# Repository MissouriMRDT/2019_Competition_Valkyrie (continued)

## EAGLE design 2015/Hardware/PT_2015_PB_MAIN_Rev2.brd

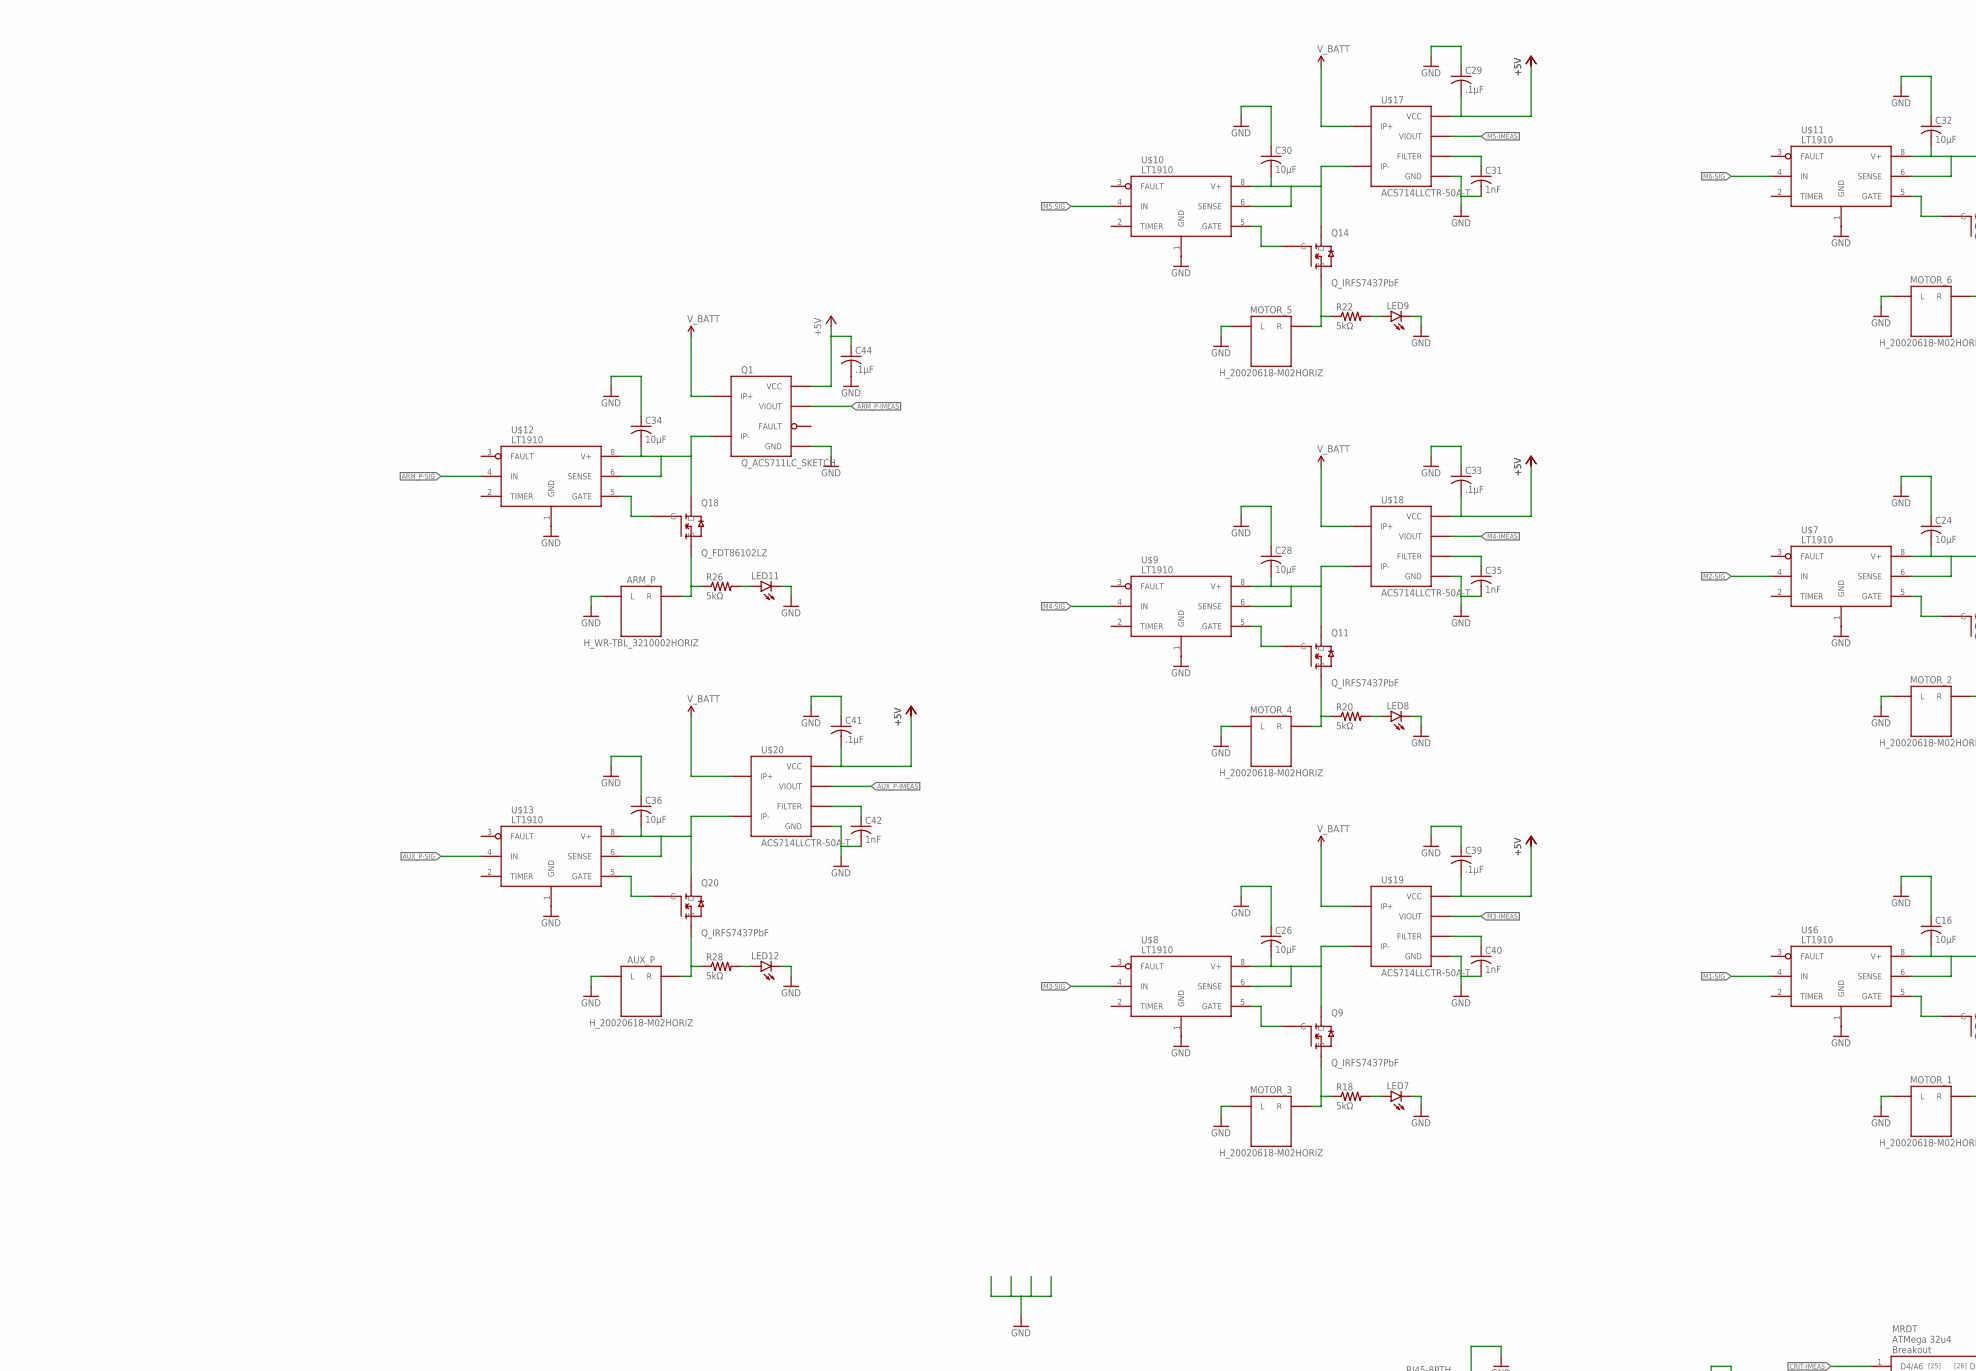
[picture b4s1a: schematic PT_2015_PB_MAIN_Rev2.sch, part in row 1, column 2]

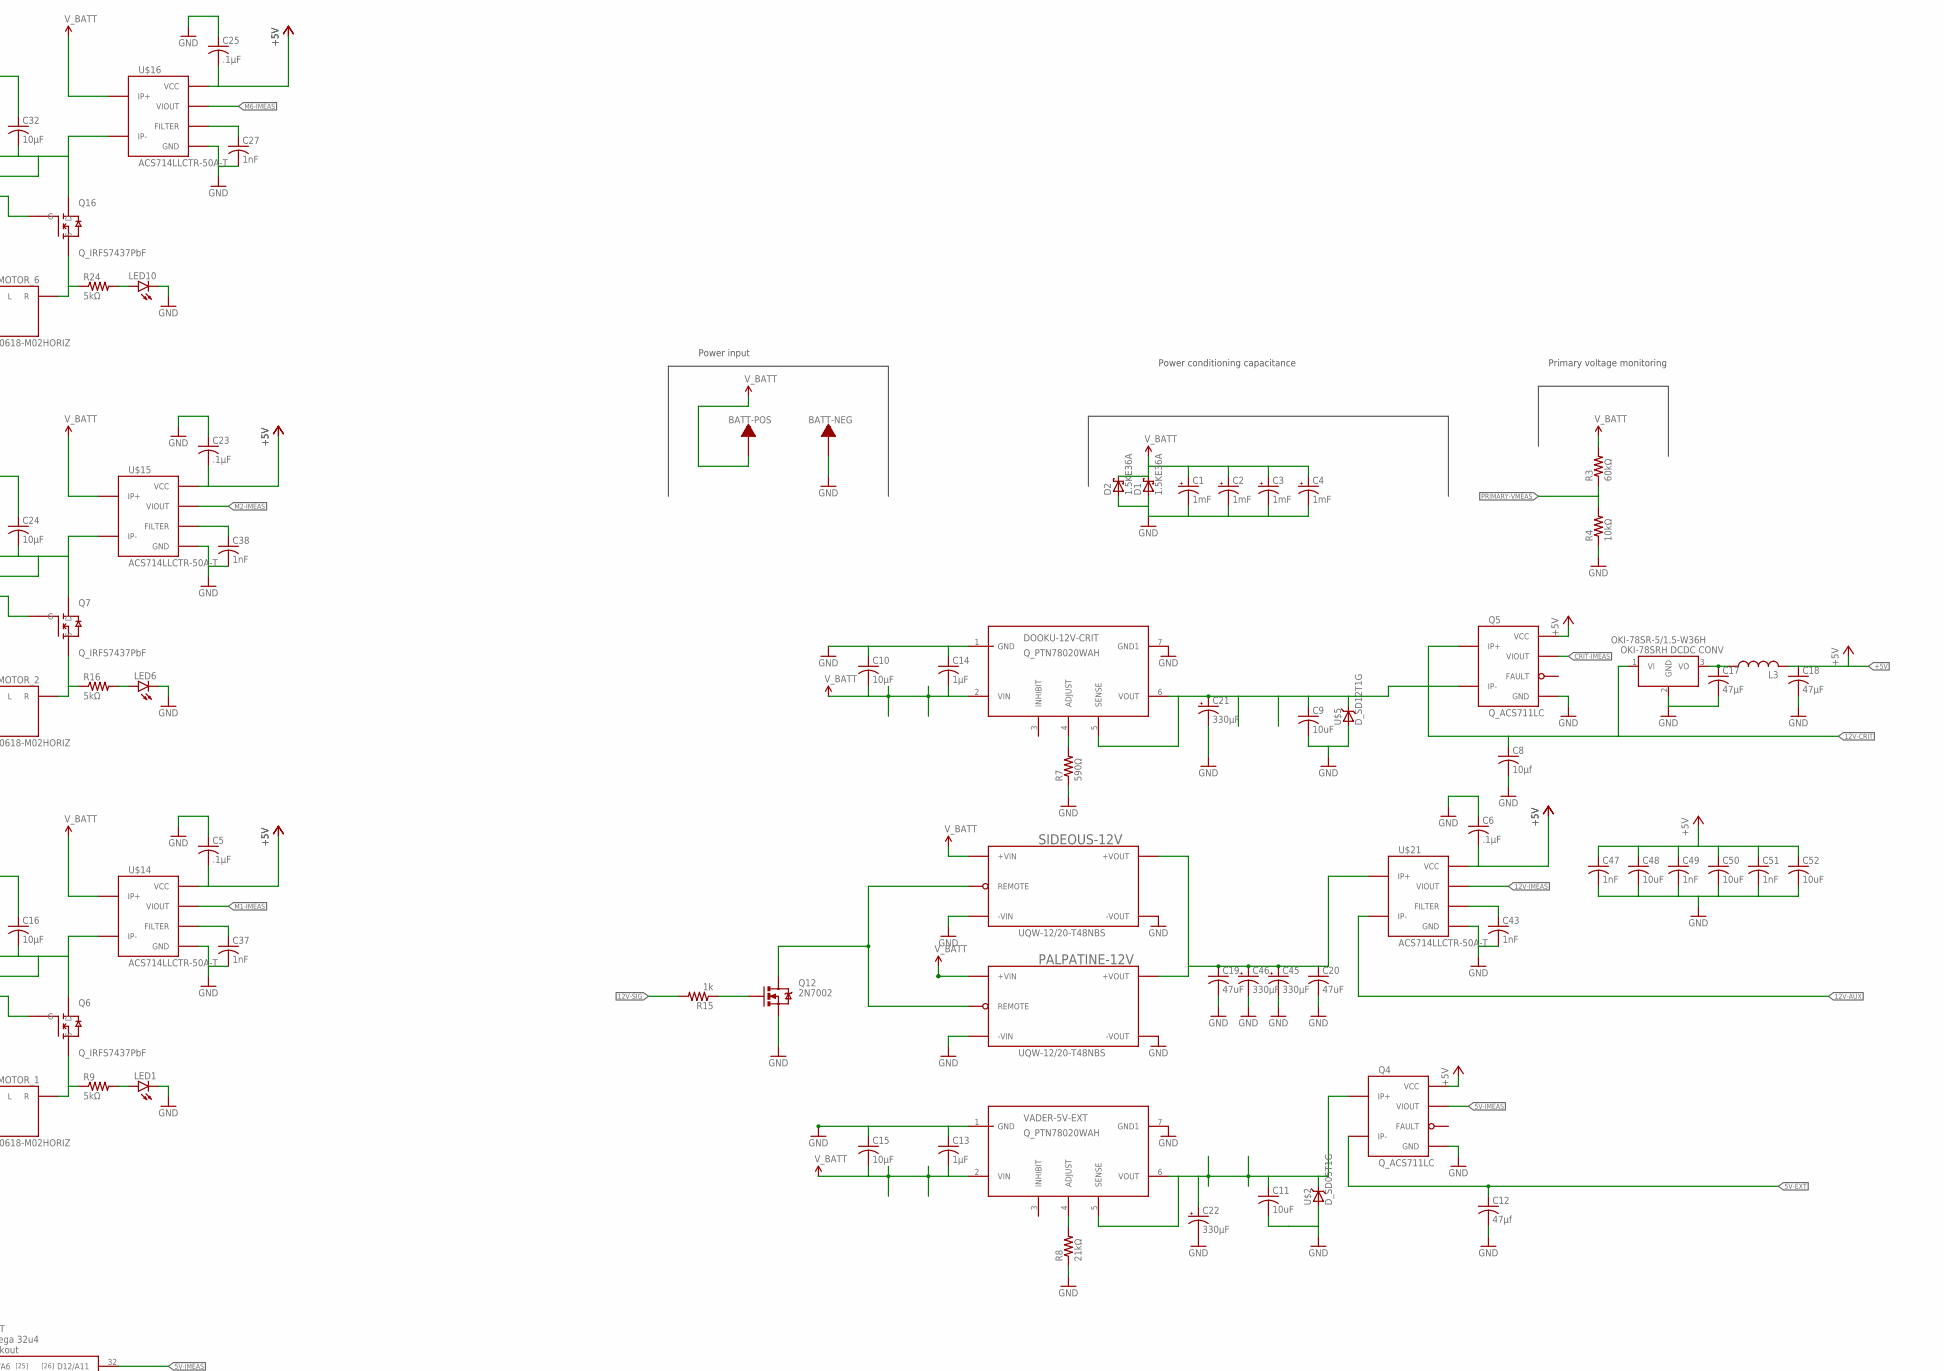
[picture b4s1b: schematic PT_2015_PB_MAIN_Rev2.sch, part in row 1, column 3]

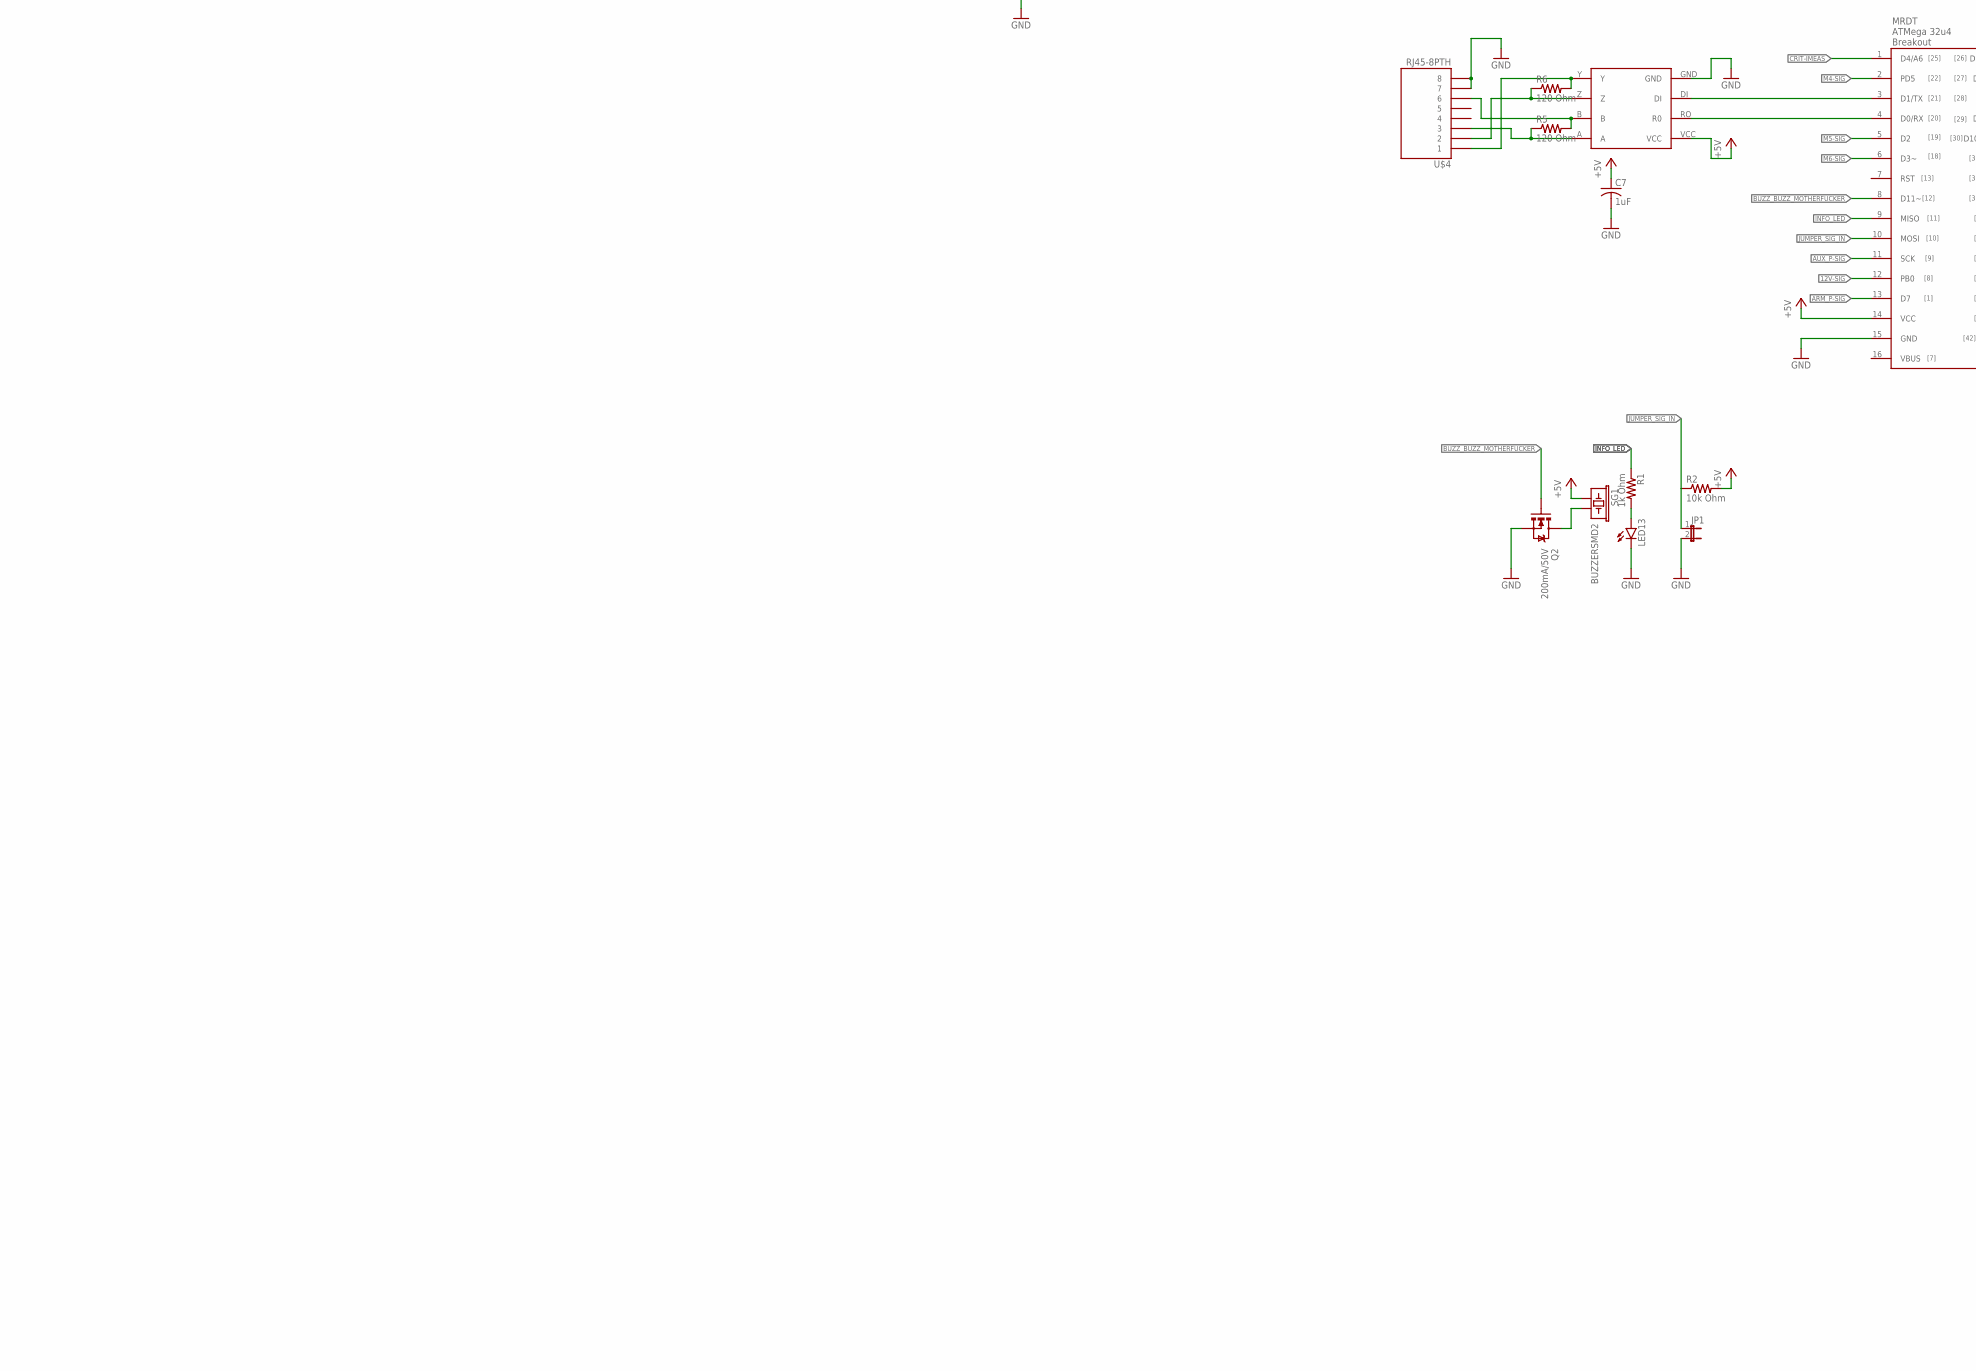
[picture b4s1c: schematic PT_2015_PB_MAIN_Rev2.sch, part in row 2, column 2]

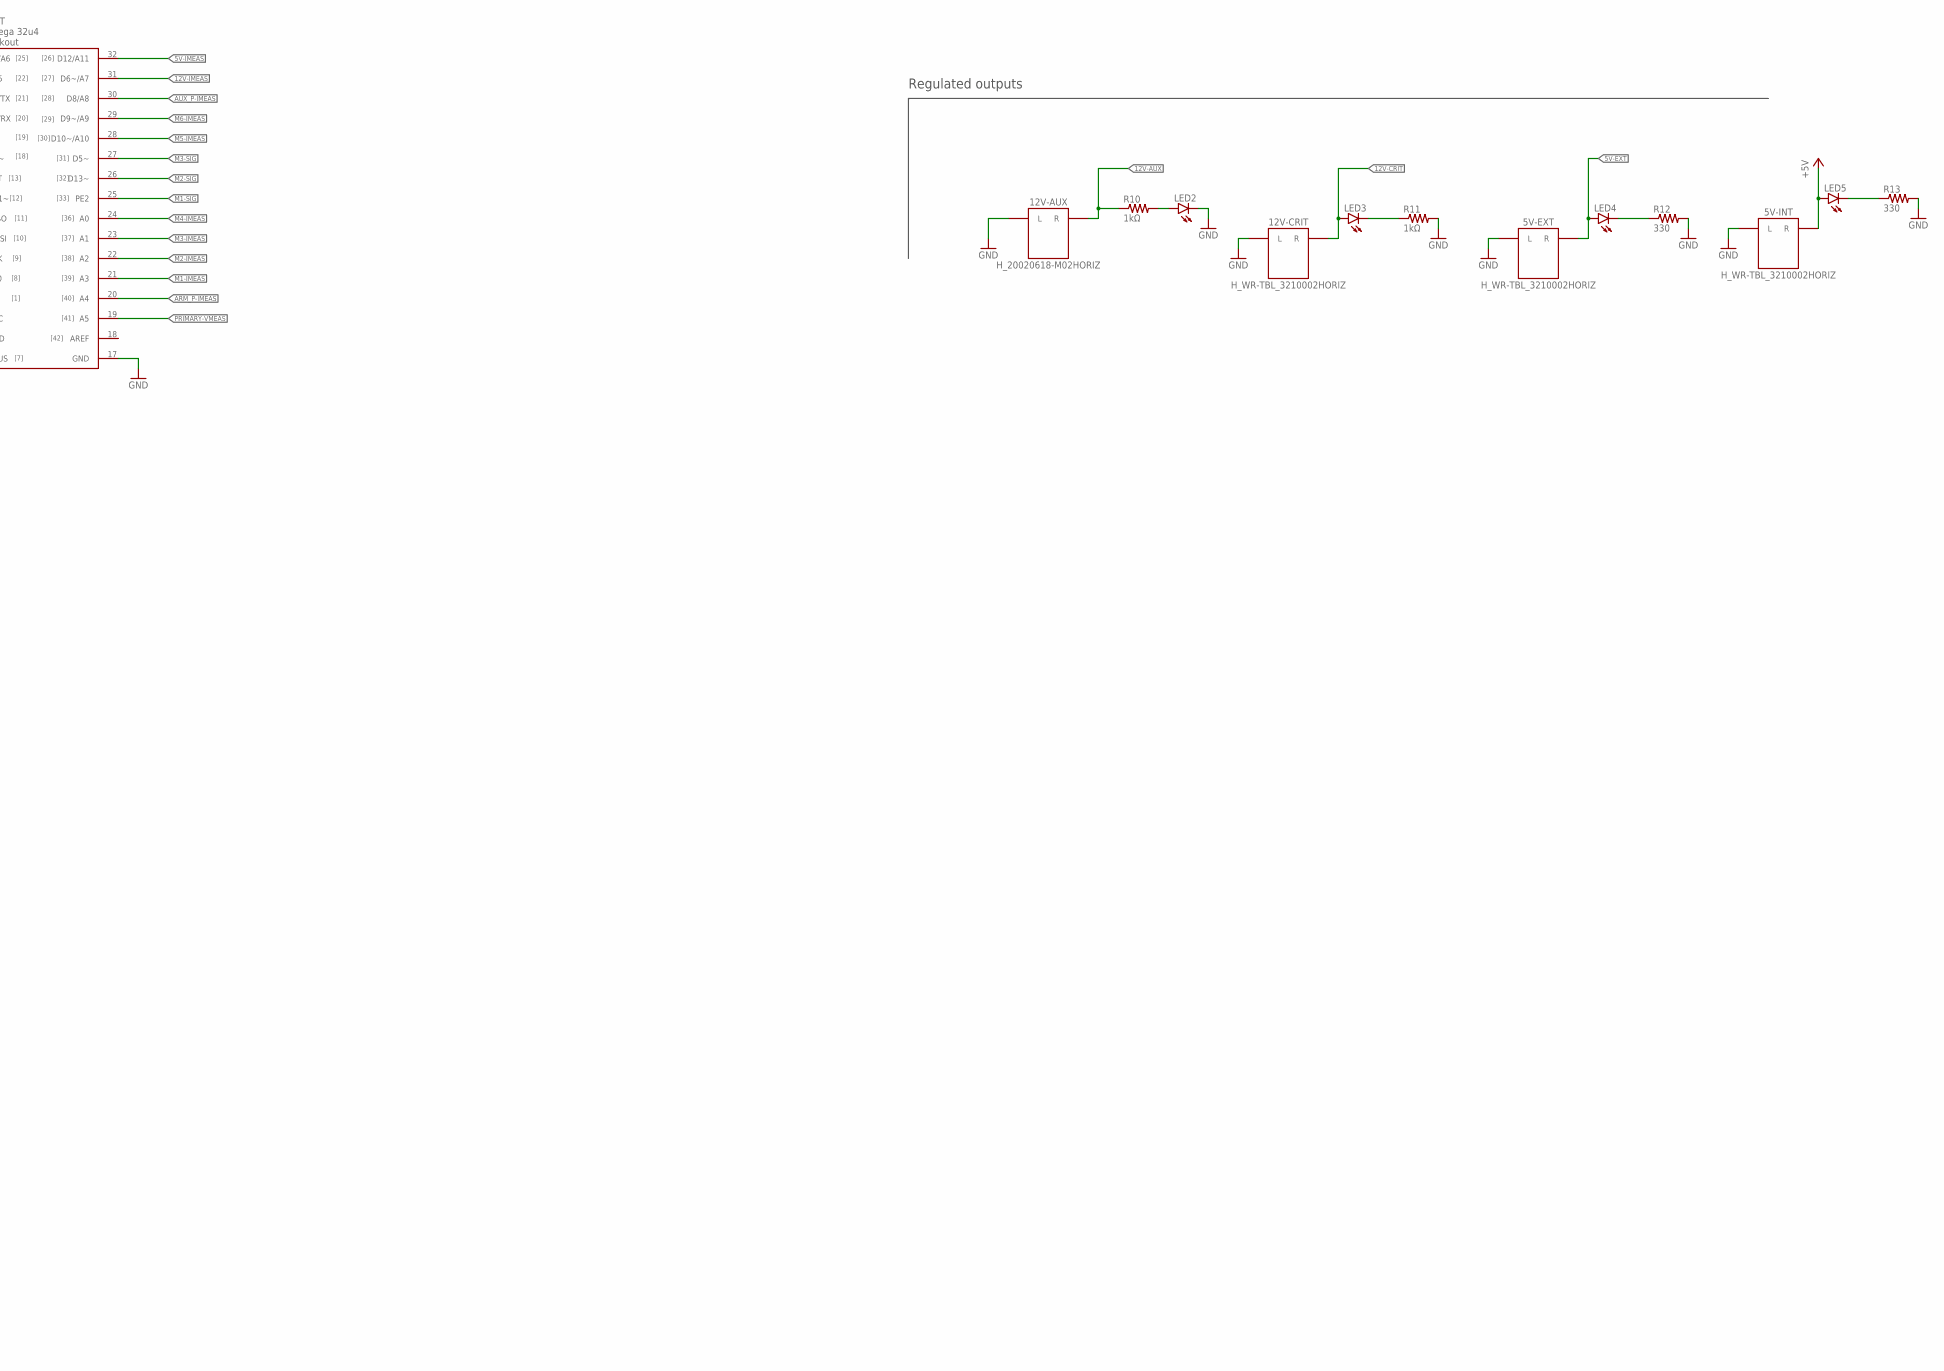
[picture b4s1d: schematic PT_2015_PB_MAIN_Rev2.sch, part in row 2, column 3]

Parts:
5V-EXT, 5V-INT, 12V-CRIT: H_WR-TBL_3210002HORIZ; 691322110002
12V-AUX: H_20020618-M02HORIZ; 20020618-M02
ARM_P: H_WR-TBL_3210002HORIZ; 691322110002
AUX_P: H_20020618-M02HORIZ; 20020618-M02
BATT-NEG: TERMINAL_HOLE; LARGE_TERMINAL_HOLE
BATT-POS: TERMINAL_HOLE; LARGE_TERMINAL_HOLE
C1, C2, C3, C4: 1mF; C_12.5MM
C5, C6, C23, C25, C29, C33, C39, C41, C44: .1µF; C1206
C7: 1uF; C1206
C8: 10µf; C1206
C9, C11, C48, C50, C52: 10uF; C1206
C10, C15, C16, C24, C26, C28, C30, C32, C34, C36: 10µF; C1206
C12: 47µf; C1206
C13, C14: 1µF; C1206
C17, C18: 47µF; C1206
C19, C20: 47uF; C1206
C21, C22, C45, C46: 330µF; E5-8,5
C27, C31, C35, C37, C38, C40, C42, C43, C47, C49, C51: 1nF; C1206
D1, D2: 1.5KE36A; CB429-17
DOOKU-12V-CRIT: Q_PTN78020WAH; R_PDSS-T7
JP1: JP1E; JP1
L3: L-USL8530M; L8530M
LED1, LED2, LED3, LED4, LED5, LED6, LED7, LED8, LED9, LED10, LED11, LED12: LED1206; LED-1206
LED13: LED-FKIT-1206; FKIT-LED-1206
MOTOR_1, MOTOR_2, MOTOR_3, MOTOR_4, MOTOR_5, MOTOR_6: H_20020618-M02HORIZ; 20020618-M02
OKI-78SR-5/1.5-W36H: Q_OKI-78SR; OKI-78SRH
PALPATINE-12V: UQW-12/20-T48NBS; U-T48-QB-NO_TRIM
Q1: Q_ACS711LC_SKETCH; SOIC8_ACS711_SKETCH
Q2: 200mA/50V; SOT23-3
Q4, Q5: Q_ACS711LC; SOIC8_ACS711
Q6, Q7, Q9, Q11, Q14, Q16, Q20: Q_IRFS7437PbF; D2PACK
Q12: 2N7002; SOT323
Q18: Q_FDT86102LZ; SOT-223
R1: 1k Ohm; 1206
R2: 10k Ohm; 1206
R3: 60kΩ; R1206
R4: 10kΩ; R1206
R5, R6: 120 Ohm; 1206
R7: 590Ω; R1206
R8: 21kΩ; R1206
R9, R16, R18, R20, R22, R24, R26, R28: 5kΩ; 1206
R10, R11: 1kΩ; 1206
R12, R13: 330; 1206
R15: 1k; R1206
SG1: BUZZERSMD2; BUZZER-CCV
SIDEOUS-12V: UQW-12/20-T48NBS; U-T48-QB-NO_TRIM
U$1: 32U4_BREAKOUT; 32U4_MCU_DIP
U$2: D_SD05T1G; SOD-323
U$3: MAX3077; MAX3070E
U$4: RJ45-8PTH; RJ45-8
U$5: D_SD12T1G; SOD-323
U$6, U$7, U$8, U$9, U$10, U$11, U$12, U$13: LT1910; SO8
U$14, U$15, U$16, U$17, U$18, U$19, U$20: ACS714LLCTR-50A-T; SOIC8_ACS711_SKETCH
U$21: ACS714LLCTR-50A-T; SOIC8_ACS711
U$22: TEST
VADER-5V-EXT: Q_PTN78020WAH; R_PDSS-T7

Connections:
5V-EXT: 5V-EXT.R, C12.1, LED4.A, Q4.4 (IP-)
5V-IMEAS: Q4.7 (VIOUT), U$1.32 (D12/A11)
12V-AUX: 12V-AUX.R1 (R), 12V-AUX.R2 (R), R10.1, U$21.4 (IP-)
12V-CRIT: 12V-CRIT.R, C8.1, LED3.A, OKI-78SR-5/1.5-W36H.1 (VI), Q5.1 (IP+)
12V-IMEAS: U$1.31 (D6~/A7), U$21.7 (VIOUT)
12V-SIG: R15.2, U$1.12 (PB0)
+5V: 5V-INT.R, C5.2, C6.2, C7.1, C18.1, C23.2, C25.2, C29.2, C33.2, C39.2, C41.2, C44.1, C47.1, C48.1, C49.1, C50.1, C51.1, C52.1, L3.2, LED5.A, Q1.8 (VCC), Q4.8 (VCC), Q5.8 (VCC), R2.2, SG1.+ (1), U$1.14 (VCC), U$3.VCC, U$14.8 (VCC), U$15.8 (VCC), U$16.8 (VCC), U$17.8 (VCC), U$18.8 (VCC), U$19.8 (VCC), U$20.8 (VCC), U$21.8 (VCC)
ARM_P-IMEAS: Q1.7 (VIOUT), U$1.20 (A4)
ARM_P-SIG: U$1.13 (D7), U$12.4 (IN)
AUX_P-IMEAS: U$1.30 (D8/A8), U$20.7 (VIOUT)
AUX_P-SIG: U$1.11 (SCK), U$13.4 (IN)
BUZZ_BUZZ_MOTHERFUCKER: Q2.1 (G), U$1.8 (D11~)
CRIT-IMEAS: Q5.7 (VIOUT), U$1.1 (D4/A6)
GND: 5V-EXT.L, 5V-INT.L, 12V-AUX.L1 (L), 12V-AUX.L2 (L), 12V-CRIT.L, ARM_P.L, AUX_P.L1 (L), AUX_P.L2 (L), BATT-NEG.P$1, C1.-, C2.-, C3.-, C4.-, C5.1, C6.1, C7.2, C8.2, C9.2, C10.1, C11.2, C12.2, C13.1, C14.1, C15.1, C16.1, C17.2, C18.2, C19.2, C20.2, C21.-, C22.-, C23.1, C24.1, C25.1, C26.1, C27.2, C28.1, C29.1, C30.1, C31.2, C32.1, C33.1, C34.1, C35.2, C36.1, C37.2, C38.2, C39.1, C40.2, C41.1, C42.2, C43.2, C44.2, C45.-, C46.-, C47.2, C48.2, C49.2, C50.2, C51.2, C52.2, D1.A, D2.A, DOOKU-12V-CRIT.1 (GND), DOOKU-12V-CRIT.7 (GND1), JP1.2, LED1.C, LED2.C, LED6.C, LED7.C, LED8.C, LED9.C, LED10.C, LED11.C, LED12.C, LED13.C, MOTOR_1.L1 (L), MOTOR_1.L2 (L), MOTOR_2.L1 (L), MOTOR_2.L2 (L), MOTOR_3.L1 (L), MOTOR_3.L2 (L), MOTOR_4.L1 (L), MOTOR_4.L2 (L), MOTOR_5.L1 (L), MOTOR_5.L2 (L), MOTOR_6.L1 (L), MOTOR_6.L2 (L), OKI-78SR-5/1.5-W36H.2 (GND), PALPATINE-12V.3 (-VIN), PALPATINE-12V.4 (-VOUT), Q1.5 (GND), Q2.2 (S), Q4.5 (GND), Q5.5 (GND), Q12.2 (S), R4.1, R7.1, R8.1, R11.2, R12.2, R13.2, SIDEOUS-12V.3 (-VIN), SIDEOUS-12V.4 (-VOUT), U$1.15 (GND), U$1.17 (GND), U$2.2 (A), U$3.GND, U$4.7, U$4.8, U$5.2 (A), U$6.1 (GND), U$7.1 (GND), U$8.1 (GND), U$9.1 (GND), U$10.1 (GND), U$11.1 (GND), U$12.1 (GND), U$13.1 (GND), U$14.5 (GND), U$15.5 (GND), U$16.5 (GND), U$17.5 (GND), U$18.5 (GND), U$19.5 (GND), U$20.5 (GND), U$21.5 (GND), VADER-5V-EXT.1 (GND), VADER-5V-EXT.7 (GND1)
INFO_LED: R1.1, U$1.9 (MISO)
JUMPER_SIG_IN: JP1.1, R2.1, U$1.10 (MOSI)
M1-IMEAS: U$1.21 (A3), U$14.7 (VIOUT)
M1-SIG: U$1.25 (PE2), U$6.4 (IN)
M2-IMEAS: U$1.22 (A2), U$15.7 (VIOUT)
M2-SIG: U$1.26 (D13~), U$7.4 (IN)
M3-IMEAS: U$1.23 (A1), U$19.7 (VIOUT)
M3-SIG: U$1.27 (D5~), U$8.4 (IN)
M4-IMEAS: U$1.24 (A0), U$18.7 (VIOUT)
M4-SIG: U$1.2 (PD5), U$9.4 (IN)
M5-IMEAS: U$1.28 (D10~/A10), U$17.7 (VIOUT)
M5-SIG: U$1.5 (D2), U$10.4 (IN)
M6-IMEAS: U$1.29 (D9~/A9), U$16.7 (VIOUT)
M6-SIG: U$1.6 (D3~), U$11.4 (IN)
unnamed: C37.1, U$14.6 (FILTER)
unnamed: C38.1, U$15.6 (FILTER)
unnamed: LED3.C, R11.1
unnamed: PALPATINE-12V.2 (REMOTE), Q12.3 (D), SIDEOUS-12V.2 (REMOTE)
unnamed: LED4.C, R12.1
unnamed: LED5.C, R13.1
unnamed: C19.1, C20.1, C45.+, C46.+, PALPATINE-12V.8 (+VOUT), SIDEOUS-12V.8 (+VOUT), U$21.1 (IP+)
unnamed: Q2.3 (D), SG1.- (2)
unnamed: DOOKU-12V-CRIT.4 (ADJUST), R7.2
unnamed: LED13.A, R1.2
unnamed: C43.1, U$21.6 (FILTER)
unnamed: R6.2, U$3.Y, U$4.1
unnamed: C11.1, C22.+, Q4.1 (IP+), U$2.1 (C), VADER-5V-EXT.5 (SENSE), VADER-5V-EXT.6 (VOUT)
unnamed: C27.1, U$16.6 (FILTER)
unnamed: R6.1, U$3.Z, U$4.2
unnamed: R5.2, U$3.B, U$4.6
unnamed: R5.1, U$3.A, U$4.3
unnamed: U$1.3 (D1/TX), U$3.DI
unnamed: C31.1, U$17.6 (FILTER)
unnamed: C35.1, U$18.6 (FILTER)
unnamed: C40.1, U$19.6 (FILTER)
unnamed: C42.1, U$20.6 (FILTER)
unnamed: C24.2, Q7.TAB (D), U$7.6 (SENSE), U$7.8 (V+), U$15.4 (IP-)
unnamed: MOTOR_2.R1 (R), MOTOR_2.R2 (R), Q7.2 (S), R16.1
unnamed: Q7.1 (G), U$7.5 (GATE)
unnamed: LED6.A, R16.2
unnamed: R8.2, VADER-5V-EXT.4 (ADJUST)
unnamed: C9.1, C21.+, DOOKU-12V-CRIT.5 (SENSE), DOOKU-12V-CRIT.6 (VOUT), Q5.4 (IP-), U$5.1 (C)
unnamed: LED1.A, R9.2
unnamed: C16.2, Q6.TAB (D), U$6.6 (SENSE), U$6.8 (V+), U$14.4 (IP-)
unnamed: MOTOR_1.R1 (R), MOTOR_1.R2 (R), Q6.2 (S), R9.1
unnamed: Q6.1 (G), U$6.5 (GATE)
unnamed: C26.2, Q9.TAB (D), U$8.6 (SENSE), U$8.8 (V+), U$19.4 (IP-)
unnamed: MOTOR_3.R1 (R), MOTOR_3.R2 (R), Q9.2 (S), R18.1
unnamed: LED2.A, R10.2
unnamed: Q9.1 (G), U$8.5 (GATE)
unnamed: LED7.A, R18.2
unnamed: C28.2, Q11.TAB (D), U$9.6 (SENSE), U$9.8 (V+), U$18.4 (IP-)
unnamed: MOTOR_4.R1 (R), MOTOR_4.R2 (R), Q11.2 (S), R20.1
unnamed: Q11.1 (G), U$9.5 (GATE)
unnamed: LED8.A, R20.2
unnamed: C30.2, Q14.TAB (D), U$10.6 (SENSE), U$10.8 (V+), U$17.4 (IP-)
unnamed: MOTOR_5.R1 (R), MOTOR_5.R2 (R), Q14.2 (S), R22.1
unnamed: Q14.1 (G), U$10.5 (GATE)
unnamed: LED9.A, R22.2
unnamed: C32.2, Q16.TAB (D), U$11.6 (SENSE), U$11.8 (V+), U$16.4 (IP-)
unnamed: MOTOR_6.R1 (R), MOTOR_6.R2 (R), Q16.2 (S), R24.1
unnamed: Q16.1 (G), U$11.5 (GATE)
unnamed: LED10.A, R24.2
unnamed: C34.2, Q1.4 (IP-), Q18.2 (D), Q18.4 (D), U$12.6 (SENSE), U$12.8 (V+)
unnamed: ARM_P.R, Q18.3 (S), R26.1
unnamed: Q18.1 (G), U$12.5 (GATE)
unnamed: LED11.A, R26.2
unnamed: C36.2, Q20.TAB (D), U$13.6 (SENSE), U$13.8 (V+), U$20.4 (IP-)
unnamed: AUX_P.R1 (R), AUX_P.R2 (R), Q20.2 (S), R28.1
unnamed: Q20.1 (G), U$13.5 (GATE)
unnamed: LED12.A, R28.2
unnamed: C17.1, L3.1, OKI-78SR-5/1.5-W36H.3 (VO)
unnamed: Q12.1 (G), R15.1
PRIMARY-VMEAS: R3.1, R4.2, U$1.19 (A5)
RXD: U$1.4 (D0/RX), U$3.RO (R0)
V_BATT: BATT-POS.P$1, C1.+, C2.+, C3.+, C4.+, C10.2, C13.2, C14.2, C15.2, D1.C, D2.C, DOOKU-12V-CRIT.2 (VIN), PALPATINE-12V.1 (+VIN), Q1.1 (IP+), R3.2, SIDEOUS-12V.1 (+VIN), U$14.1 (IP+), U$15.1 (IP+), U$16.1 (IP+), U$17.1 (IP+), U$18.1 (IP+), U$19.1 (IP+), U$20.1 (IP+), VADER-5V-EXT.2 (VIN)

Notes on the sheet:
Primary voltage monitoring
Power conditioning capacitance
Power input
Regulated outputs

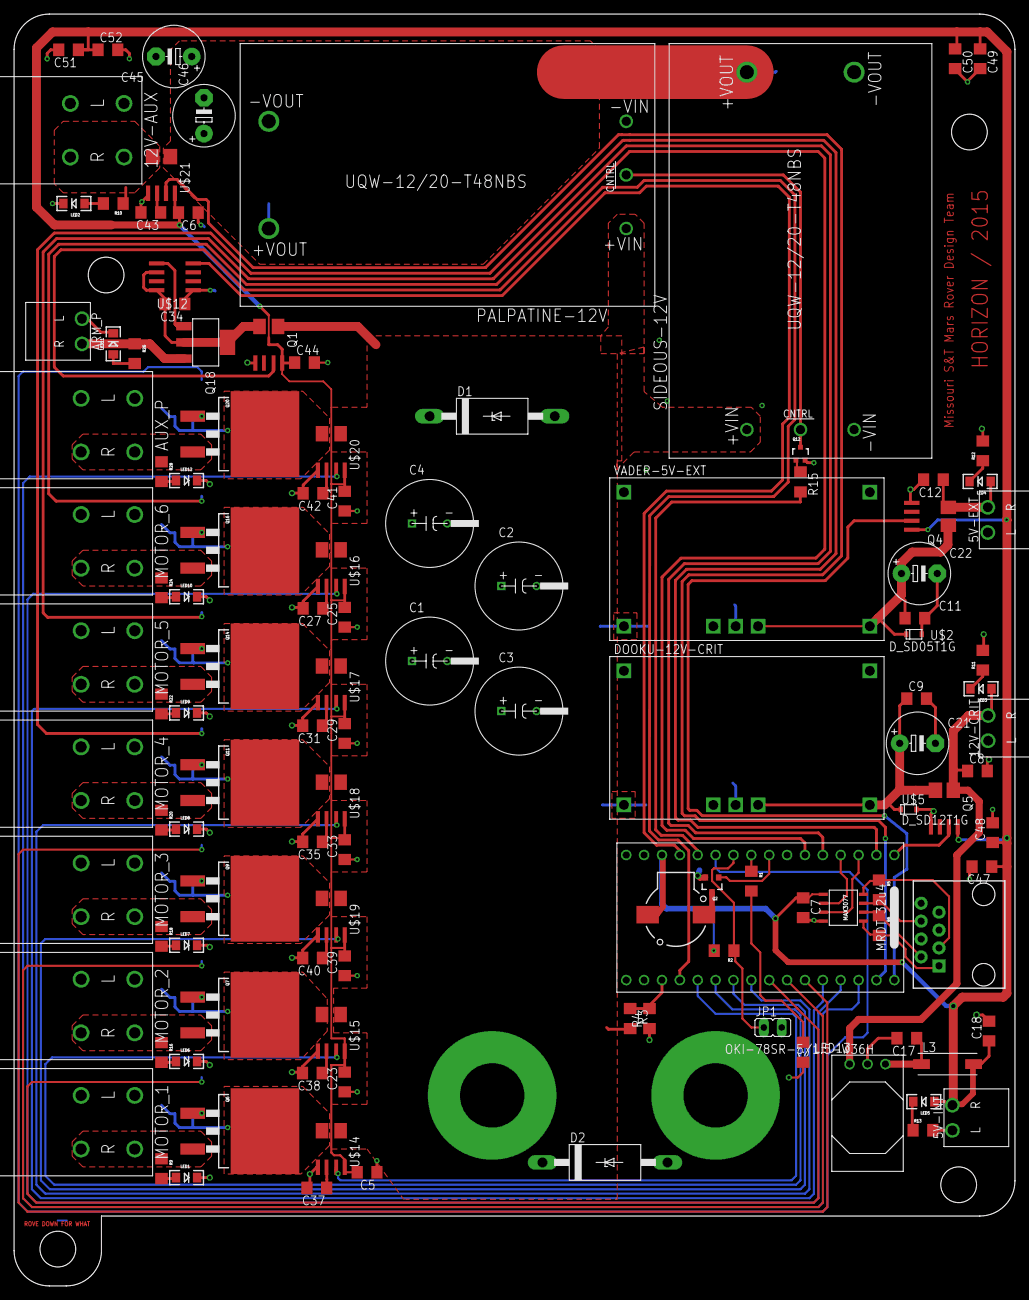
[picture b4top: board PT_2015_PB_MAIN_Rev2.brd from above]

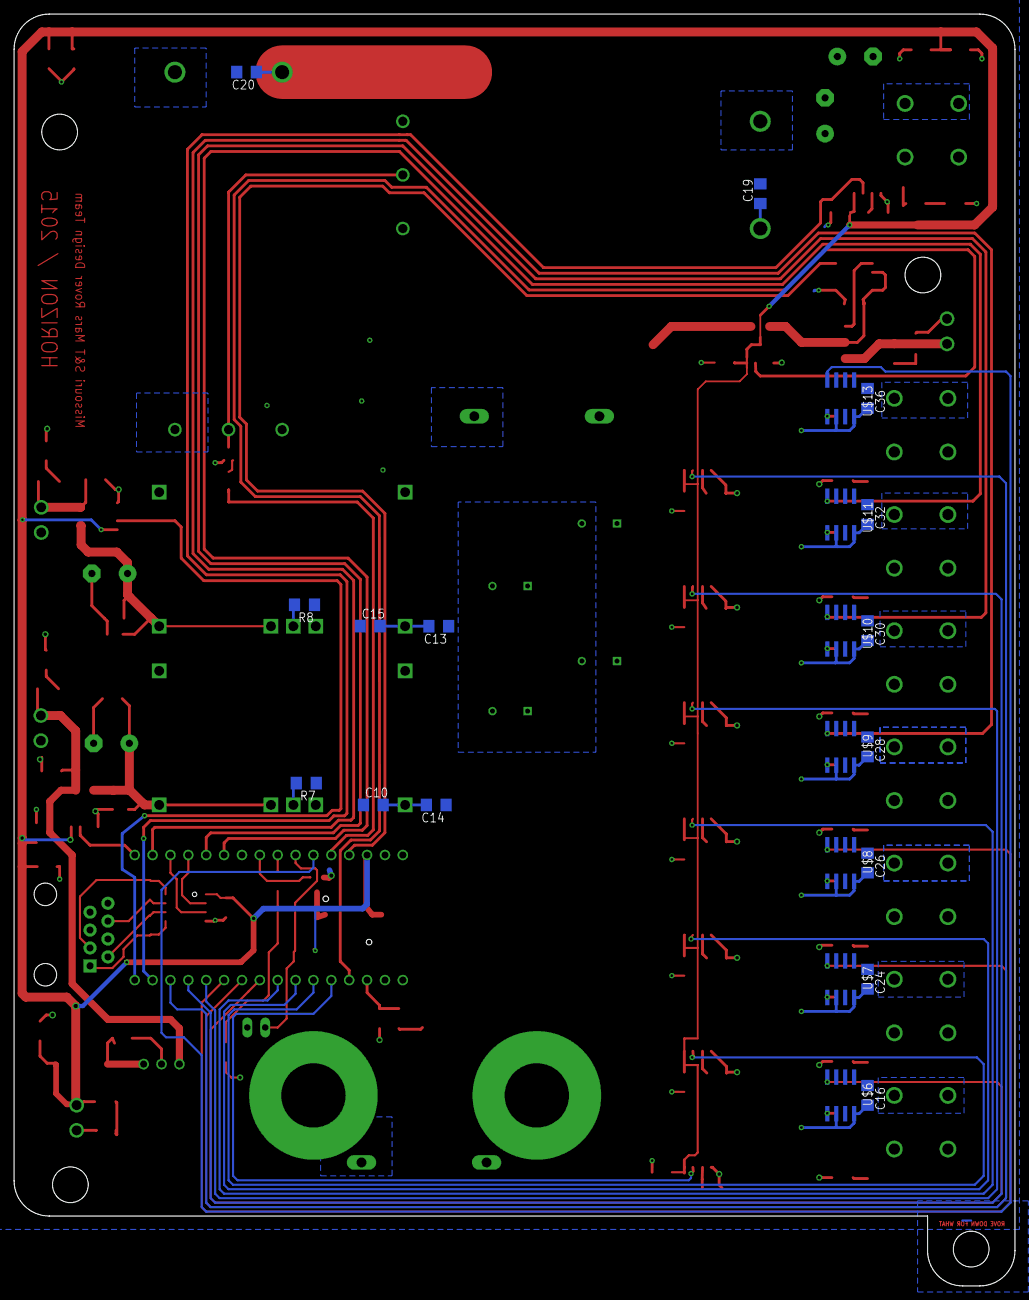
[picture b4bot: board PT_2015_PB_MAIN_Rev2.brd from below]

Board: 2 copper layers, 142.2 x 180.7 mm, 145 parts (22 on the bottom side), 90 nets.

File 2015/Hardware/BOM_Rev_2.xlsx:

Qty | Value | Device | Package | Parts | Description | DIGIKEY_PN | PROD_ID
6 |  | C-USC1206 | C1206 | C9, C10, C11, C15, C19, C20 | CAPACITOR, American symbol
1 |  | L-USL3216C | L3216C | L3 | INDUCTOR, American symbol
12 |  | LED1206 | LED-1206 | LED1, LED2, LED3, LED4, LED5, LED6, LED7, LED8, LED9, LED10, LED11, LED12 | LEDs
1 |  | R-US_R1206 | R1206 | R15 | RESISTOR, American symbol
9 | .1µF | C-USC1206 | C1206 | C5, C6, C23, C25, C29, C33, C39, C41, C44 | CAPACITOR, American symbol
2 | 1.5KE36A | 15KEXX | CB429-17 | D1, D2 | DIODE
1 | 10kO | R-US_R1206 | R1206 | R4 | RESISTOR, American symbol
8 | 10µF | C-USC1206 | C1206 | C16, C24, C26, C28, C30, C32, C34, C36 | CAPACITOR, American symbol
2 | 120 Ohm | RESISTOR1206 | 1206 | R5, R6 | Resistor
12 | 1kO | RESISTOR1206 | 1206 | R9, R10, R11, R12, R13, R16, R18, R20, R22, R24, R26, R28 | Resistor
4 | 1mF | C_POL12.5MM_NORMAL | C_12.5MM | C1, C2, C3, C4 | Alum Elect. Cap with 10mm diameter, 5mm lead spacing and 0.7mm lead diameter
8 | 1nF | C-USC0805 | C0805 | C27, C31, C35, C37, C38, C40, C42, C43 | CAPACITOR, American symbol
1 | 1uF | C-USC1206 | C1206 | C7 | CAPACITOR, American symbol
2 | 2.2µF | C-USC1206 | C1206 | C13, C14 | CAPACITOR, American symbol
1 | 21kO | R-US_R1206 | R1206 | R8 | RESISTOR, American symbol
1 | 2N7002 | MOSFET-NCHANNEL2N7002PW | SOT323 | Q12 | Common NMOSFET Parts |  | TRANS-11151
1 | 32U4_BREAKOUT | 32U4_BREAKOUT | 32U4_MCU_DIP | U$1
3 | 330µF | CPOL-USE5-8.5 | E5-8,5 | C21, C22, C45 | POLARIZED CAPACITOR, American symbol
2 | 47µF | C-USC1206 | C1206 | C17, C18 | CAPACITOR, American symbol
2 | 47µf | C-USC1206 | C1206 | C8, C12 | CAPACITOR, American symbol
1 | 590O | R-US_R1206 | R1206 | R7 | RESISTOR, American symbol
1 | 70kO | R-US_R1206 | R1206 | R3 | RESISTOR, American symbol
1 | ACS714LLCTR-50A-T | Q_ACS714 | SOIC8_ACS711 | U$21 | Sketch variant has increased clearance for traces. | 620-1683-1-ND
7 | ACS714LLCTR-50A-T | Q_ACS714_SKETCH | SOIC8_ACS711_SKETCH | U$14, U$15, U$16, U$17, U$18, U$19, U$20 | Sketch variant has increased clearance for traces. | 620-1683-1-ND
2 | D_SD12T1G | D_SD12T1G | SOD-323 | U$2, U$5 | 12V or 5V Zener
8 | H_20020618-M02 | H_20020618-M02 | 20020618-M02 | 12V-AUX, AUX_P, MOTOR_1, MOTOR_2, MOTOR_3, MOTOR_4, MOTOR_5, MOTOR_6 | 20020618-M02* header pin from FCI. Rated up to 32A
4 | H_WR-TBL_321*0002HORIZ | H_WR-TBL_321*0002HORIZ | 691322110002 | 5V-EXT, 5V-INT, 12V-CRIT, ARM_P | Wurth Electronic's 2-pin 10A pluggable screw terminal headers. Vertical and Hor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 | 732-2769-ND
8 | LT1910 | LT1910 | SO8 | U$6, U$7, U$8, U$9, U$10, U$11, U$12, U$13
6 | L_29F0429 | L_29F0429 | L_29F0429 | L1, L4, L5, L8, L2, L6 | Through-Hole Ferrite Bead 285 Ohm @ 100MHz
1 | MAX3077 | MAX3077 | MAX3070E | U$3
2 | Q_ACS711LC | Q_ACS711LC | SOIC8_ACS711 | Q4, Q5 | ±12.5A or ±25A Hall-effect current transducer. SOIC-8 Package with fused pads.
1 | Q_ACS711LC_SKETCH | Q_ACS711LC_SKETCH | SOIC8_ACS711_SKETCH | Q1 | ±12.5A or ±25A Hall-effect current transducer. SOIC-8 Package with fused pads.
1 | Q_FDT86102LZ | Q_FDT86102LZ | SOT-223 | Q18
7 | Q_IRFS7437PbF | Q_IRF7437SMD | D2PACK | Q6, Q7, Q9, Q11, Q14, Q16, Q20 | 40V 195A N-CH MOSFET switch with heatsink
1 | Q_OKI-78SR | Q_OKI-78SR | OKI-78SRH | OKI-78SR-5/1.5-W36H | 4.95W DC/DC Converter
2 | Q_PTN78020WAH | Q_PTN78020 | R_PDSS-T7 | DOOKU-12V-CRIT, VADER-5V-EXT | TI DC/DC converter 36Vin - Adjustable output
1 | RJ45-8PTH | RJ45-8PTH | RJ45-8 | U$4 | RJ45 Jack
2 | TERMINAL_HOLE | TERMINAL_HOLE | LARGE_TERMINAL_HOLE | BATT-NEG, BATT-POS
2 | UQW-12/20-T48NBS | UQW-12/20-T48NBS | U-T48-QB-NO_TRIM | PALPATINE-12V, SIDEOUS-12V
